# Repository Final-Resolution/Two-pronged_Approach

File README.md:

# Two-pronged_Approach
Use 74HC595 chip to drive two IN-12 Nixie tubes, and theoretically unlimited cascading!

Sorry, I still need some time to prepare the readme file. Let's see what it looks like!

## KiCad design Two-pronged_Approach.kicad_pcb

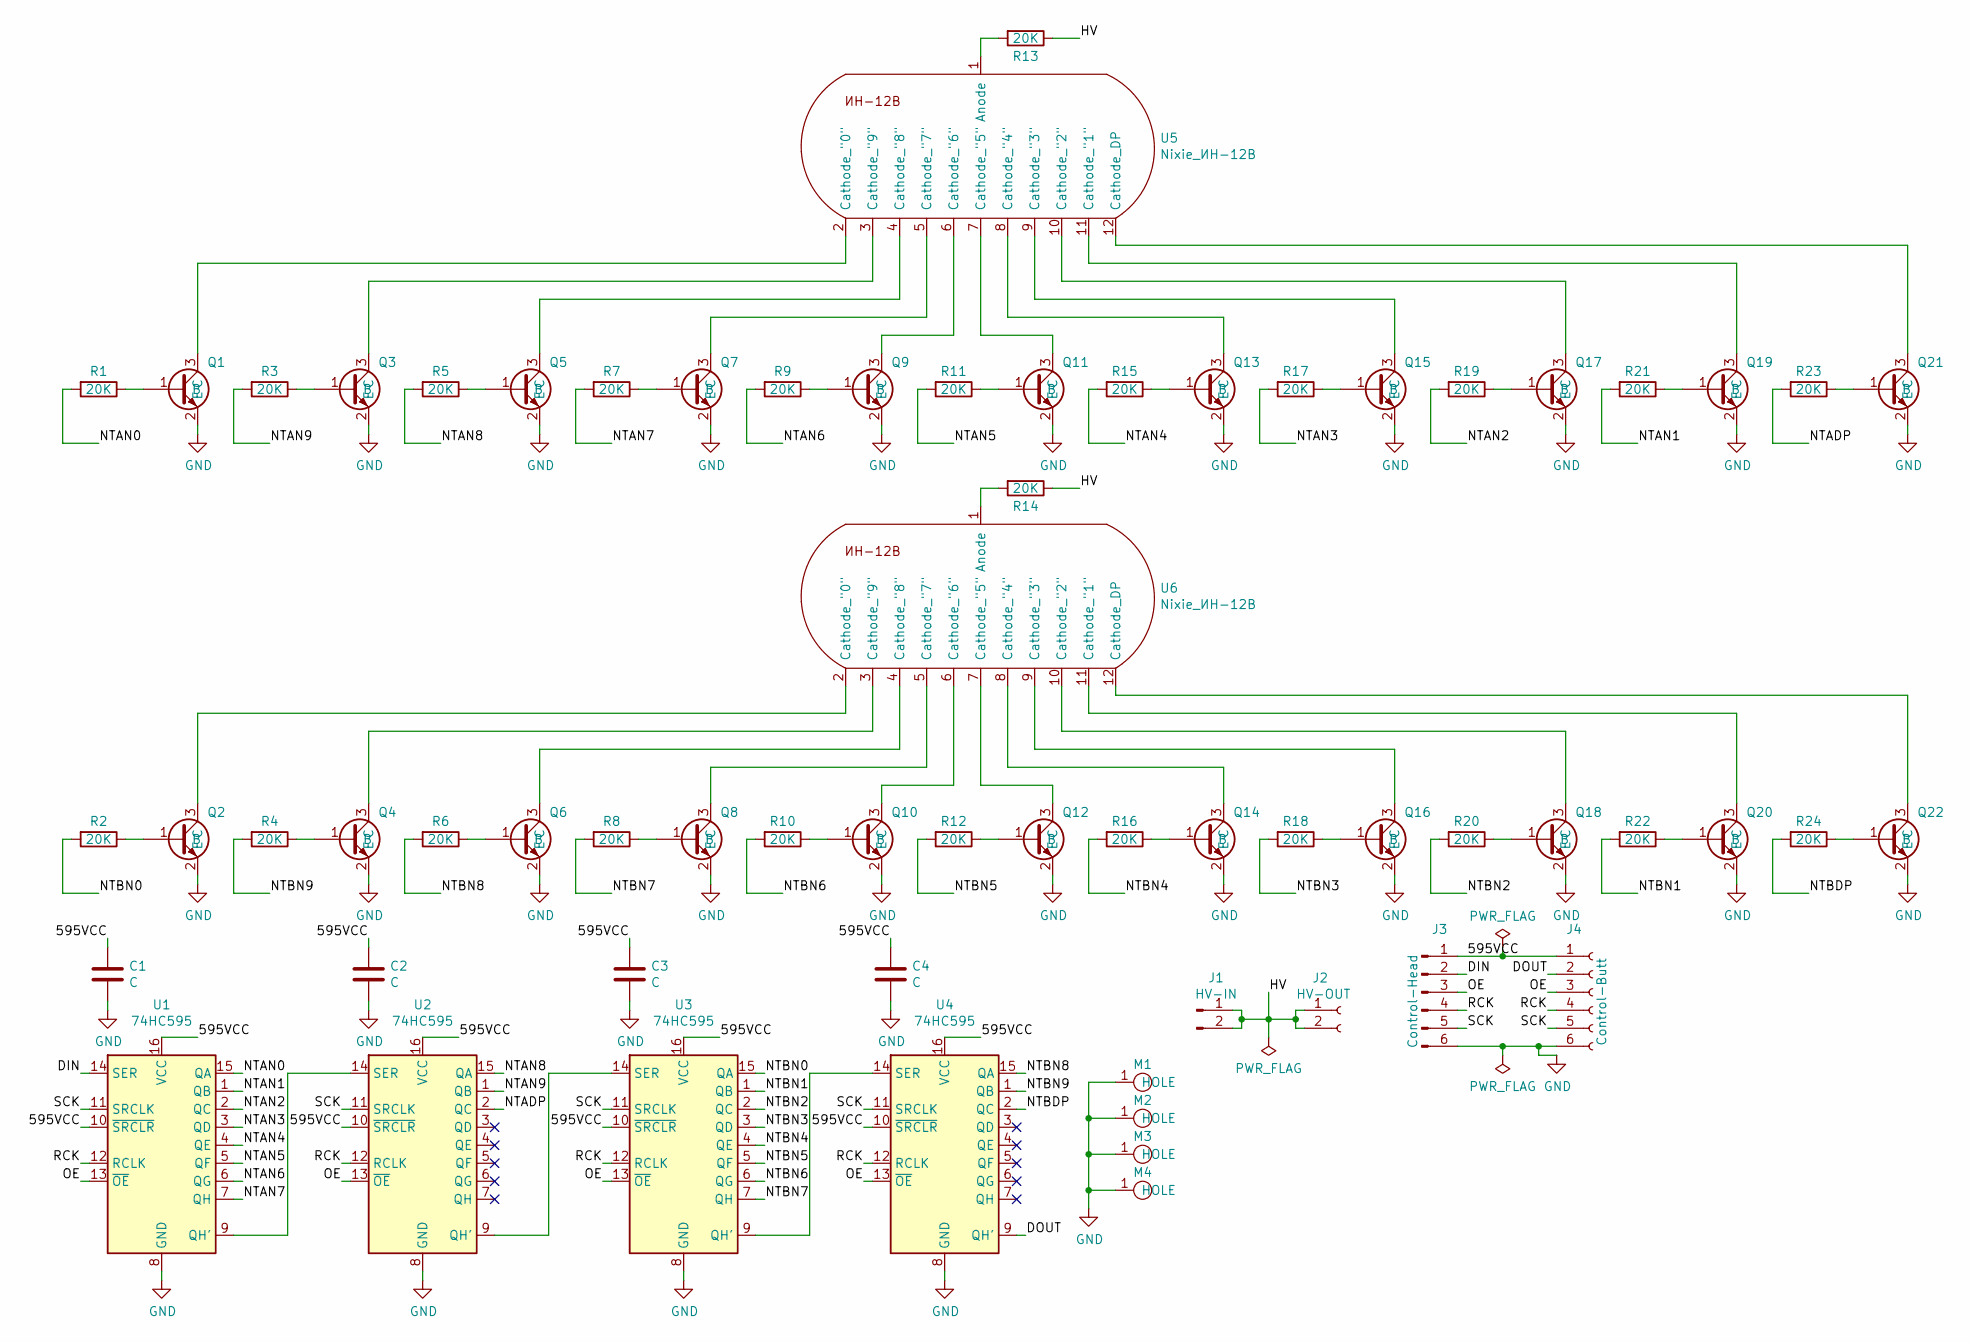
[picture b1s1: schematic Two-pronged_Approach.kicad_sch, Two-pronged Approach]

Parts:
C1, C2, C3, C4: C; C_0603_1608Metric_Pad1.05x0.95mm_HandSolder
J1: HV-IN; PinHeader_1x02_P2.54mm_Horizontal_IN
J2: HV-OUT; PinHeader_1x02_P2.54mm_Horizontal_OUT
J3: Control-Head; PinHeader_1x06_P2.54mm_Horizontal_IN
J4: Control-Butt; PinHeader_1x06_P2.54mm_Horizontal_OUT
M1, M2, M3, M4: M3-Hole; MountingHole_3mm_Pad_Via
Q1, Q2, Q3, Q4, Q5, Q6, Q7, Q8, Q9, Q10, Q11, Q12, Q13, Q14, Q15, Q16, Q17, Q18, Q19, Q20, Q21, Q22: MMBTA42; SOT-23
R1, R2, R3, R4, R5, R6, R7, R8, R9, R10, R11, R12, R15, R16, R17, R18, R19, R20, R21, R22, R23, R24: 20K; R_0603_1608Metric_Pad1.05x0.95mm_HandSolder
R13, R14: 20K; R_1206_3216Metric_Pad1.42x1.75mm_HandSolder
U1, U2, U3, U4: 74HC595; SOP-16_4.55x10.3mm_P1.27mm
U5, U6: Nixie_ИН-12B; IN-12B-Use-Pin-Header-3

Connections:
/595VCC: C1.1, C2.1, C3.1, C4.1, J3.1, J4.1, U1.10 (~SRCLR), U1.16 (VCC), U2.10 (~SRCLR), U2.16 (VCC), U3.10 (~SRCLR), U3.16 (VCC), U4.10 (~SRCLR), U4.16 (VCC)
/DIN: J3.2, U1.14 (SER)
/DOUT: J4.2, U4.9 (QH')
/HV: J1.1, J1.2, J2.1, J2.2, R13.1, R14.1
/NTADP: R23.2, U2.2 (QC)
/NTAN0: R1.2, U1.15 (QA)
/NTAN1: R21.2, U1.1 (QB)
/NTAN2: R19.2, U1.2 (QC)
/NTAN3: R17.2, U1.3 (QD)
/NTAN4: R15.2, U1.4 (QE)
/NTAN5: R11.2, U1.5 (QF)
/NTAN6: R9.2, U1.6 (QG)
/NTAN7: R7.2, U1.7 (QH)
/NTAN8: R5.2, U2.15 (QA)
/NTAN9: R3.2, U2.1 (QB)
/NTBDP: R24.2, U4.2 (QC)
/NTBN0: R2.2, U3.15 (QA)
/NTBN1: R22.2, U3.1 (QB)
/NTBN2: R20.2, U3.2 (QC)
/NTBN3: R18.2, U3.3 (QD)
/NTBN4: R16.2, U3.4 (QE)
/NTBN5: R12.2, U3.5 (QF)
/NTBN6: R10.2, U3.6 (QG)
/NTBN7: R8.2, U3.7 (QH)
/NTBN8: R6.2, U4.15 (QA)
/NTBN9: R4.2, U4.1 (QB)
/OE: J3.3, J4.3, U1.13 (~OE), U2.13 (~OE), U3.13 (~OE), U4.13 (~OE)
/RCK: J3.4, J4.4, U1.12 (RCLK), U2.12 (RCLK), U3.12 (RCLK), U4.12 (RCLK)
/SCK: J3.5, J4.5, U1.11 (SRCLK), U2.11 (SRCLK), U3.11 (SRCLK), U4.11 (SRCLK)
GND: C1.2, C2.2, C3.2, C4.2, J3.6, J4.6, M1.1 (HOLE), M2.1 (HOLE), M3.1 (HOLE), M4.1 (HOLE), Q1.2 (E), Q2.2 (E), Q3.2 (E), Q4.2 (E), Q5.2 (E), Q6.2 (E), Q7.2 (E), Q8.2 (E), Q9.2 (E), Q10.2 (E), Q11.2 (E), Q12.2 (E), Q13.2 (E), Q14.2 (E), Q15.2 (E), Q16.2 (E), Q17.2 (E), Q18.2 (E), Q19.2 (E), Q20.2 (E), Q21.2 (E), Q22.2 (E), U1.8 (GND), U2.8 (GND), U3.8 (GND), U4.8 (GND)
unnamed: Q1.1 (B), R1.1
unnamed: Q1.3 (C), U5.2 (Cathode_"0")
unnamed: Q2.1 (B), R2.1
unnamed: Q2.3 (C), U6.2 (Cathode_"0")
unnamed: Q3.1 (B), R3.1
unnamed: Q3.3 (C), U5.3 (Cathode_"9")
unnamed: Q4.1 (B), R4.1
unnamed: Q4.3 (C), U6.3 (Cathode_"9")
unnamed: Q5.1 (B), R5.1
unnamed: Q5.3 (C), U5.4 (Cathode_"8")
unnamed: Q6.1 (B), R6.1
unnamed: Q6.3 (C), U6.4 (Cathode_"8")
unnamed: Q7.1 (B), R7.1
unnamed: Q7.3 (C), U5.5 (Cathode_"7")
unnamed: Q8.1 (B), R8.1
unnamed: Q8.3 (C), U6.5 (Cathode_"7")
unnamed: Q9.1 (B), R9.1
unnamed: Q9.3 (C), U5.6 (Cathode_"6")
unnamed: Q10.1 (B), R10.1
unnamed: Q10.3 (C), U6.6 (Cathode_"6")
unnamed: Q11.1 (B), R11.1
unnamed: Q11.3 (C), U5.7 (Cathode_"5")
unnamed: Q12.1 (B), R12.1
unnamed: Q12.3 (C), U6.7 (Cathode_"5")
unnamed: Q13.1 (B), R15.1
unnamed: Q13.3 (C), U5.8 (Cathode_"4")
unnamed: Q14.1 (B), R16.1
unnamed: Q14.3 (C), U6.8 (Cathode_"4")
unnamed: Q15.1 (B), R17.1
unnamed: Q15.3 (C), U5.9 (Cathode_"3")
unnamed: Q16.1 (B), R18.1
unnamed: Q16.3 (C), U6.9 (Cathode_"3")
unnamed: Q17.1 (B), R19.1
unnamed: Q17.3 (C), U5.10 (Cathode_"2")
unnamed: Q18.1 (B), R20.1
unnamed: Q18.3 (C), U6.10 (Cathode_"2")
unnamed: Q19.1 (B), R21.1
unnamed: Q19.3 (C), U5.11 (Cathode_"1")
unnamed: Q20.1 (B), R22.1
unnamed: Q20.3 (C), U6.11 (Cathode_"1")
unnamed: Q21.1 (B), R23.1
unnamed: Q21.3 (C), U5.12 (Cathode_DP)
unnamed: Q22.1 (B), R24.1
unnamed: Q22.3 (C), U6.12 (Cathode_DP)
unnamed: U1.9 (QH'), U2.14 (SER)
unnamed: U2.9 (QH'), U3.14 (SER)
unnamed: U3.9 (QH'), U4.14 (SER)
unnamed: R13.2, U5.1 (Anode)
unnamed: R14.2, U6.1 (Anode)

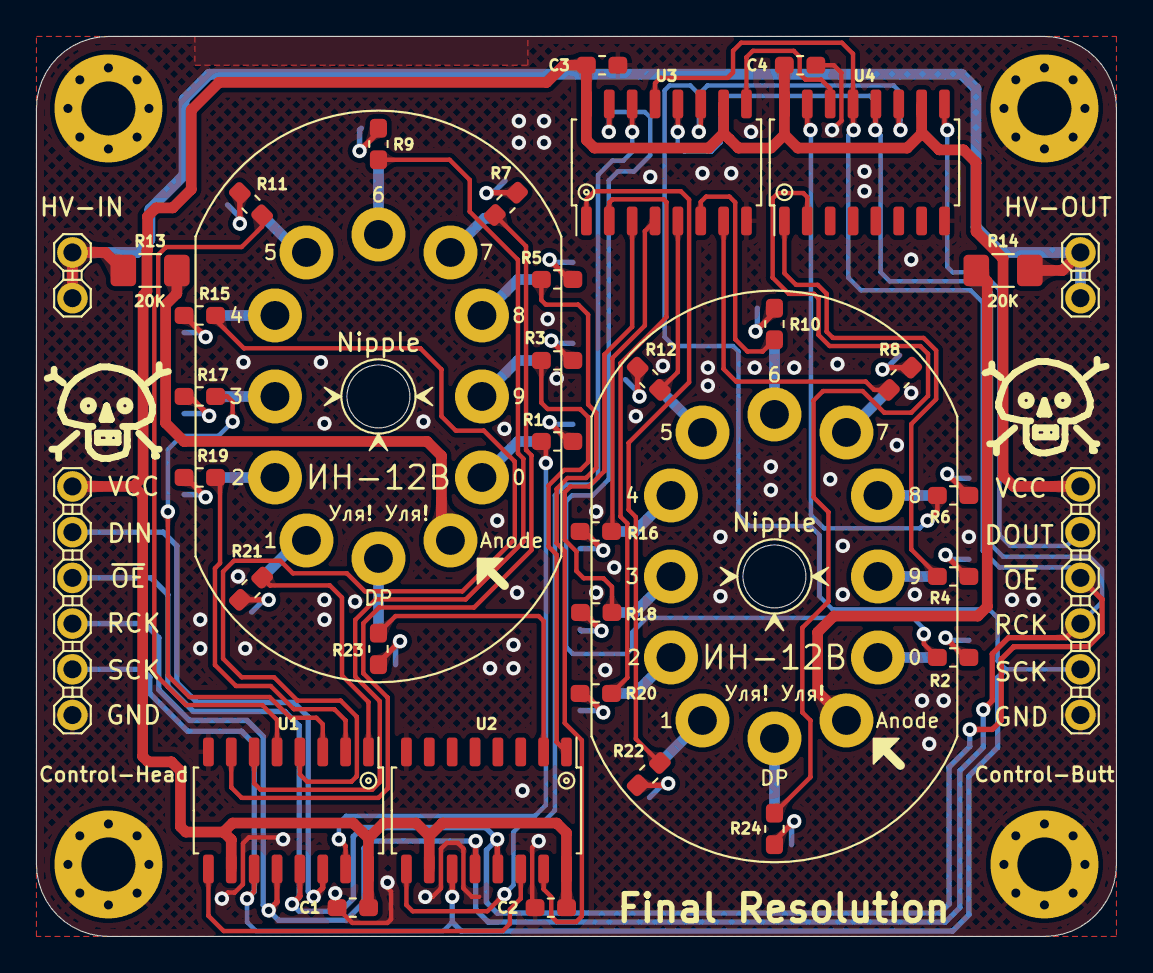
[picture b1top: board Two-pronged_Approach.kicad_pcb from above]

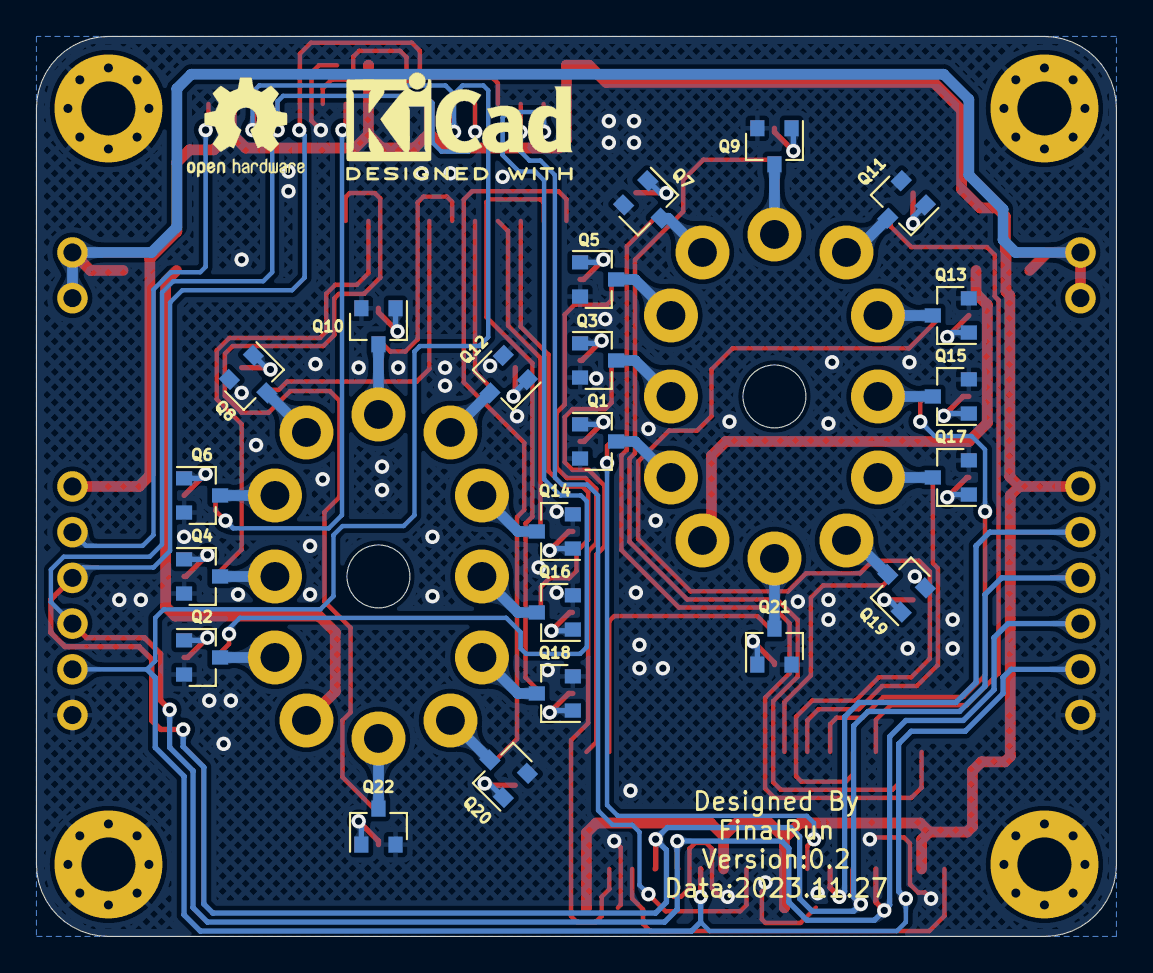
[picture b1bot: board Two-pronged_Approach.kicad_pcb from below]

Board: 2 copper layers, 60.0 x 50.0 mm, 64 parts (22 on the bottom side), 79 nets.

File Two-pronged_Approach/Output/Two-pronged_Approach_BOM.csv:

"Comment","Description","Designator","Footprint","LibRef","Pins","Quantity","PartNumber","url",
"C","desc","C1,C4,C3,C2,","C_0603_1608Metric_Pad1.05x0.95mm_HandSolder","libref","2","4","","",
"LOGO","desc","G***,","Two-pronged-Approach-Silks","libref","0","1","","",
"LOGO","desc","G***,","REV_C_Silks_Small","libref","0","1","","",
"20K","desc","R14,R13,","R_1206_3216Metric_Pad1.42x1.75mm_HandSolder","libref","2","2","","",
"20K","desc","R24,R23,R22,R21,R20,R19,R18,R17,R16,R15,R12,R11,R10,R9,R8,R7,R6,R5,R4,R3,R2,R1,","R_0603_1608Metric_Pad1.05x0.95mm_HandSolder","libref","2","22","","",
"Symbol_Danger_CopperTop_Small","desc","REF**,REF**,","Symbol_Danger_CopperTop_Small","libref","0","2","","",
"74HC595","desc","U4,U3,U2,U1,","SOP-16_4.55x10.3mm_P1.27mm","libref","16","4","","",
"LOGO","desc","G***,","FinalR-logo-Mask","libref","0","1","","",
"MMBTA42","desc","Q22,Q21,Q20,Q19,Q18,Q17,Q16,Q15,Q14,Q13,Q12,Q11,Q10,Q9,Q8,Q7,Q6,Q5,Q4,Q3,Q2,Q1,","SOT-23","libref","3","22","","",
"Through Hole Items ",
"HV-IN","desc","J1,","PinHeader_1x02_P2.54mm_Horizontal_IN","libref","2","1","","",
"HV-OUT","desc","J2,","PinHeader_1x02_P2.54mm_Horizontal_OUT","libref","2","1","","",
"Head","desc","J3,","PinHeader_1x06_P2.54mm_Horizontal_IN","libref","6","1","","",
"Butt","desc","J4,","PinHeader_1x06_P2.54mm_Horizontal_OUT","libref","6","1","","",
"M3-Hole","desc","M4,M3,M2,M1,","MountingHole_3mm_Pad_Via","libref","9","4","","",
"Nixie_ИН-12B","desc","U6,U5,","IN-12B-Use-Pin-Header-3","libref","13","2","","",

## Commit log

2020-09-18 Create LICENSE
2023-11-27 提交文件
2023-11-27 添加截图
2023-11-27 添加自述文件
